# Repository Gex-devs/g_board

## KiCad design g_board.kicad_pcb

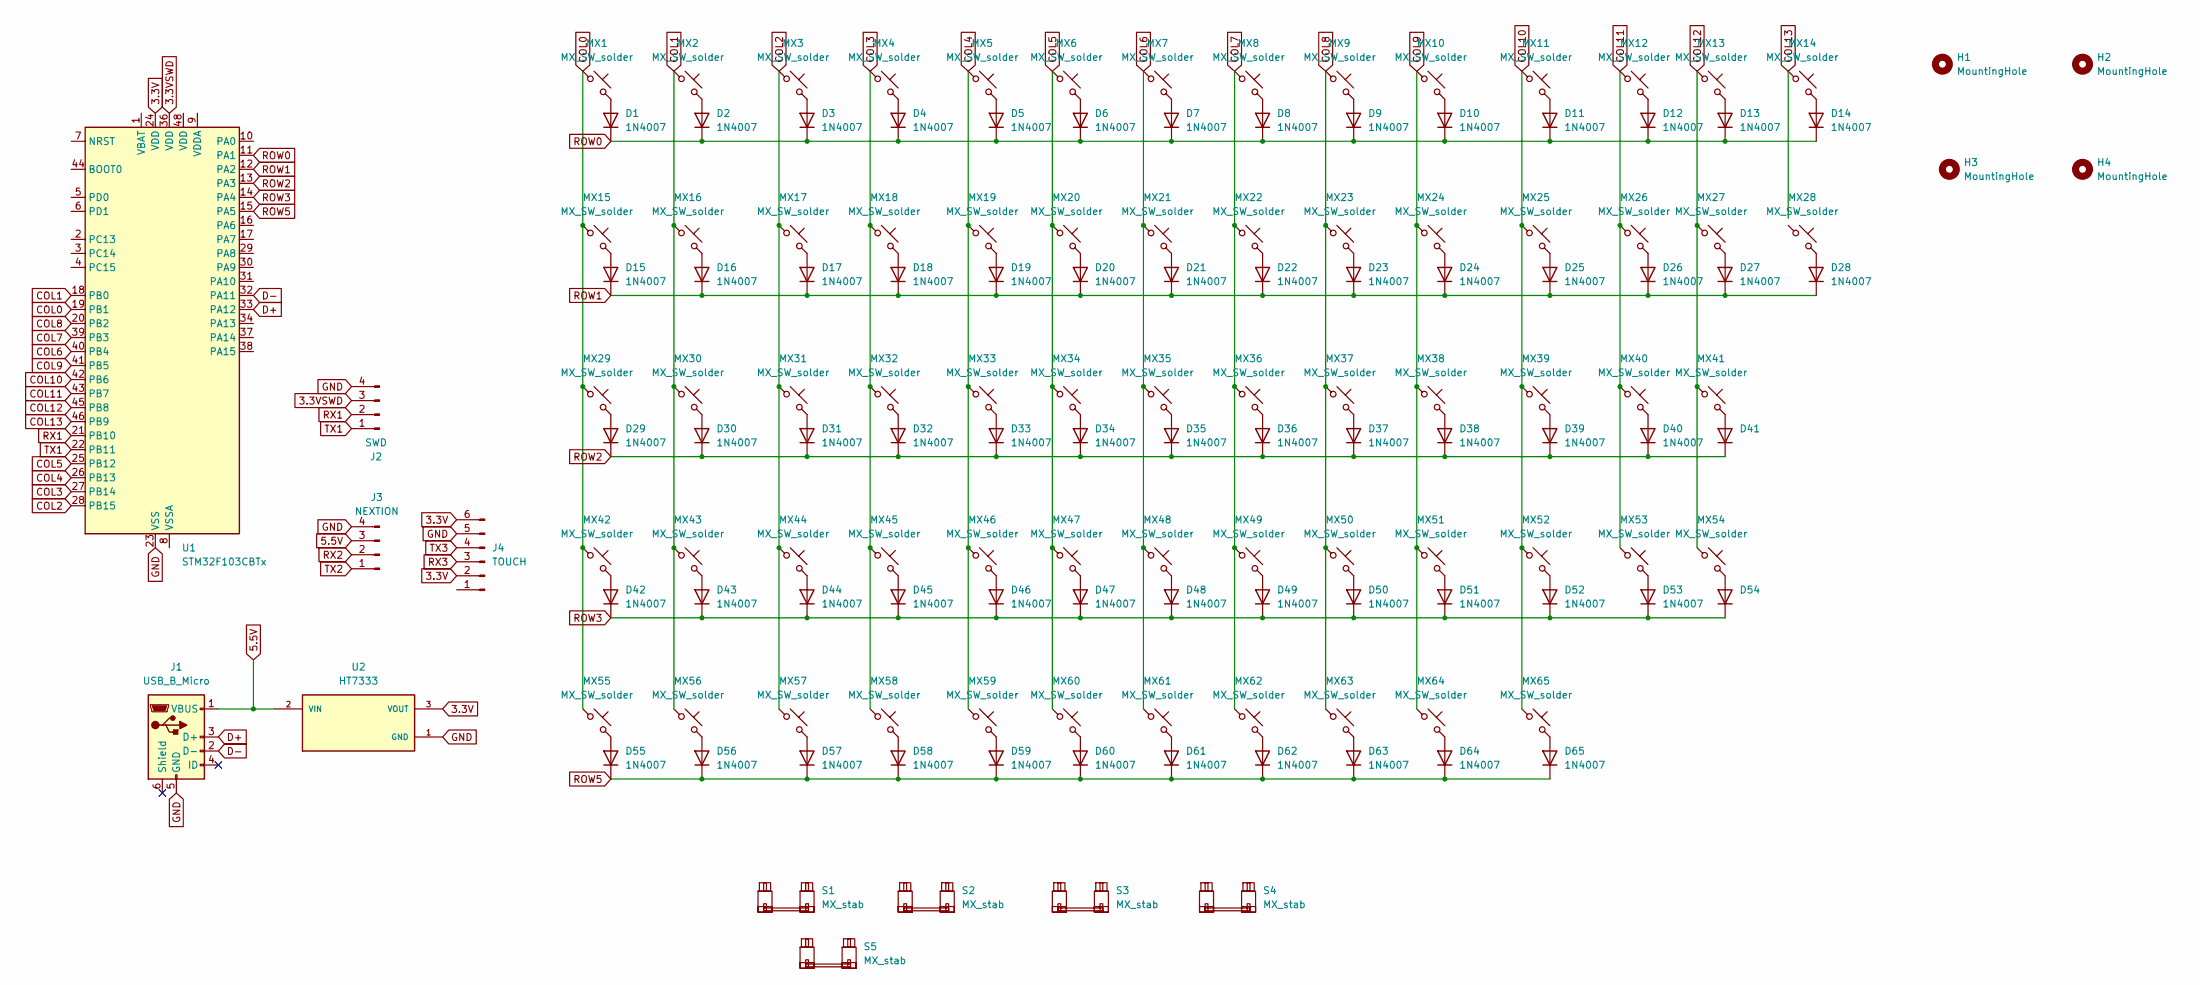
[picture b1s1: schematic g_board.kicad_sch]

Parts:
D1, D2, D3, D4, D5, D6, D7, D8, D9, D10, D11, D12, D13, D14, D15, D16, D17, D18, D19, D20, D21, D22, D23, D24, D25, D26, D27, D28, D29, D30, D31, D32, D33, D34, D35, D36, D37, D38, D39, D40, D41, D42, D43, D44, D45, D46, D47, D48, D49, D50, D51, D52, D53, D54, D55, D56, D57, D58, D59, D60, D61, D62, D63, D64, D65: 1N4007; D_DO-41_SOD81_P10.16mm_Horizontal
H1, H2, H3, H4: MountingHole; MountingHole_3.2mm_M3
J1: USB_B_Micro; USB_Micro-AB_Molex_47590-0001
J2: SWD; PinHeader_1x04_P2.54mm_Vertical
J3: NEXTION; PinHeader_1x04_P2.54mm_Vertical
J4: TOUCH; PinSocket_1x06_P2.54mm_Vertical
MX1, MX2, MX3, MX4, MX5, MX6, MX7, MX8, MX9, MX10, MX11, MX12, MX13, MX14, MX16, MX17, MX18, MX19, MX20, MX21, MX22, MX23, MX24, MX25, MX26, MX27, MX30, MX31, MX32, MX33, MX34, MX35, MX36, MX37, MX38, MX39, MX40, MX41, MX42, MX43, MX44, MX45, MX46, MX47, MX48, MX49, MX50, MX51, MX52, MX53, MX54, MX58, MX63, MX64, MX65: MX_SW_solder; SW_MX_1u
MX15, MX28: MX_SW_solder; SW_MX_1.5u
MX29: MX_SW_solder; SW_MX_1.75u
MX55, MX56, MX57, MX59, MX60, MX61, MX62: MX_SW_solder; SW_MX_1.25u
S1: MX_stab; STAB_MX_P_6.25u
S2: MX_stab; STAB_MX_P_2.75u
S3: MX_stab; STAB_MX_P_2u
S4, S5: MX_stab; STAB_MX_P_2.25u
U1: STM32F103CBTx; LQFP-48_7x7mm_P0.5mm
U2: HT7333; IC_HT7333; PARTREV 1.80

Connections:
3.3V: J4.2, J4.6, U1.24 (VDD), U2.3 (VOUT)
3.3VSWD: J2.3, U1.36 (VDD)
5.5V: J1.1 (VBUS), J3.3, U2.2 (VIN)
COL0: MX1.1, MX15.1, MX29.1, MX42.1, MX55.1, U1.19 (PB1)
COL1: MX2.1, MX16.1, MX30.1, MX43.1, MX56.1, U1.18 (PB0)
COL2: MX3.1, MX17.1, MX31.1, MX44.1, MX57.1, U1.28 (PB15)
COL3: MX4.1, MX18.1, MX32.1, MX45.1, MX58.1, U1.27 (PB14)
COL4: MX5.1, MX19.1, MX33.1, MX46.1, MX59.1, U1.26 (PB13)
COL5: MX6.1, MX20.1, MX34.1, MX47.1, MX60.1, U1.25 (PB12)
COL6: MX7.1, MX21.1, MX35.1, MX48.1, MX61.1, U1.40 (PB4)
COL7: MX8.1, MX22.1, MX36.1, MX49.1, MX62.1, U1.39 (PB3)
COL8: MX9.1, MX23.1, MX37.1, MX50.1, MX63.1, U1.20 (PB2)
COL9: MX10.1, MX24.1, MX38.1, MX51.1, MX64.1, U1.41 (PB5)
COL10: MX11.1, MX25.1, MX39.1, MX52.1, MX65.1, U1.42 (PB6)
COL11: MX12.1, MX26.1, MX40.1, MX53.1, U1.43 (PB7)
COL12: MX13.1, MX27.1, MX41.1, MX54.1, U1.45 (PB8)
COL13: MX14.1, U1.46 (PB9)
D+: J1.3 (D+), U1.33 (PA12)
D-: J1.2 (D-), U1.32 (PA11)
GND: J1.5 (GND), J2.4, J3.4, J4.5, U1.23 (VSS), U1.35 (VSS), U1.47 (VSS), U2.1 (GND)
unnamed: D1.2 (A), MX1.2
unnamed: D2.2 (A), MX2.2
unnamed: D3.2 (A), MX3.2
unnamed: D4.2 (A), MX4.2
unnamed: D5.2 (A), MX5.2
unnamed: D6.2 (A), MX6.2
unnamed: D7.2 (A), MX7.2
unnamed: D8.2 (A), MX8.2
unnamed: D9.2 (A), MX9.2
unnamed: D10.2 (A), MX10.2
unnamed: D11.2 (A), MX11.2
unnamed: D12.2 (A), MX12.2
unnamed: D13.2 (A), MX13.2
unnamed: D14.2 (A), MX14.2
unnamed: D15.2 (A), MX15.2
unnamed: D16.2 (A), MX16.2
unnamed: D17.2 (A), MX17.2
unnamed: D18.2 (A), MX18.2
unnamed: D19.2 (A), MX19.2
unnamed: D20.2 (A), MX20.2
unnamed: D21.2 (A), MX21.2
unnamed: D22.2 (A), MX22.2
unnamed: D23.2 (A), MX23.2
unnamed: D24.2 (A), MX24.2
unnamed: D25.2 (A), MX25.2
unnamed: D26.2 (A), MX26.2
unnamed: D27.2 (A), MX27.2
unnamed: D28.2 (A), MX28.2
unnamed: D29.2 (A), MX29.2
unnamed: D30.2 (A), MX30.2
unnamed: D31.2 (A), MX31.2
unnamed: D32.2 (A), MX32.2
unnamed: D33.2 (A), MX33.2
unnamed: D34.2 (A), MX34.2
unnamed: D35.2 (A), MX35.2
unnamed: D36.2 (A), MX36.2
unnamed: D37.2 (A), MX37.2
unnamed: D38.2 (A), MX38.2
unnamed: D39.2 (A), MX39.2
unnamed: D40.2 (A), MX40.2
unnamed: D41.2 (A), MX41.2
unnamed: D42.2 (A), MX42.2
unnamed: D43.2 (A), MX43.2
unnamed: D44.2 (A), MX44.2
unnamed: D45.2 (A), MX45.2
unnamed: D46.2 (A), MX46.2
unnamed: D47.2 (A), MX47.2
unnamed: D48.2 (A), MX48.2
unnamed: D49.2 (A), MX49.2
unnamed: D50.2 (A), MX50.2
unnamed: D51.2 (A), MX51.2
unnamed: D52.2 (A), MX52.2
unnamed: D53.2 (A), MX53.2
unnamed: D54.2 (A), MX54.2
unnamed: D55.2 (A), MX55.2
unnamed: D56.2 (A), MX56.2
unnamed: D57.2 (A), MX57.2
unnamed: D58.2 (A), MX58.2
unnamed: D59.2 (A), MX59.2
unnamed: D60.2 (A), MX60.2
unnamed: D61.2 (A), MX61.2
unnamed: D62.2 (A), MX62.2
unnamed: D63.2 (A), MX63.2
unnamed: D64.2 (A), MX64.2
unnamed: D65.2 (A), MX65.2
ROW0: D1.1 (K), D2.1 (K), D3.1 (K), D4.1 (K), D5.1 (K), D6.1 (K), D7.1 (K), D8.1 (K), D9.1 (K), D10.1 (K), D11.1 (K), D12.1 (K), D13.1 (K), D14.1 (K), U1.11 (PA1)
ROW1: D15.1 (K), D16.1 (K), D17.1 (K), D18.1 (K), D19.1 (K), D20.1 (K), D21.1 (K), D22.1 (K), D23.1 (K), D24.1 (K), D25.1 (K), D26.1 (K), D27.1 (K), D28.1 (K), U1.12 (PA2)
ROW2: D29.1 (K), D30.1 (K), D31.1 (K), D32.1 (K), D33.1 (K), D34.1 (K), D35.1 (K), D36.1 (K), D37.1 (K), D38.1 (K), D39.1 (K), D40.1 (K), D41.1 (K), U1.13 (PA3)
ROW3: D42.1 (K), D43.1 (K), D44.1 (K), D45.1 (K), D46.1 (K), D47.1 (K), D48.1 (K), D49.1 (K), D50.1 (K), D51.1 (K), D52.1 (K), D53.1 (K), D54.1 (K), U1.14 (PA4)
ROW5: D55.1 (K), D56.1 (K), D57.1 (K), D58.1 (K), D59.1 (K), D60.1 (K), D61.1 (K), D62.1 (K), D63.1 (K), D64.1 (K), D65.1 (K), U1.15 (PA5)
RX1: J2.2, U1.21 (PB10)
RX2: J3.2
RX3: J4.3
TX1: J2.1, U1.22 (PB11)
TX2: J3.1
TX3: J4.4

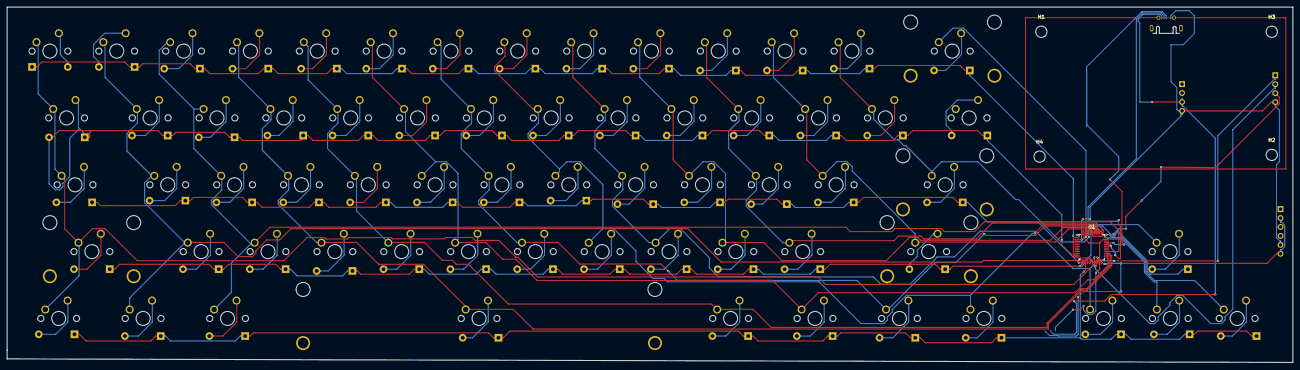
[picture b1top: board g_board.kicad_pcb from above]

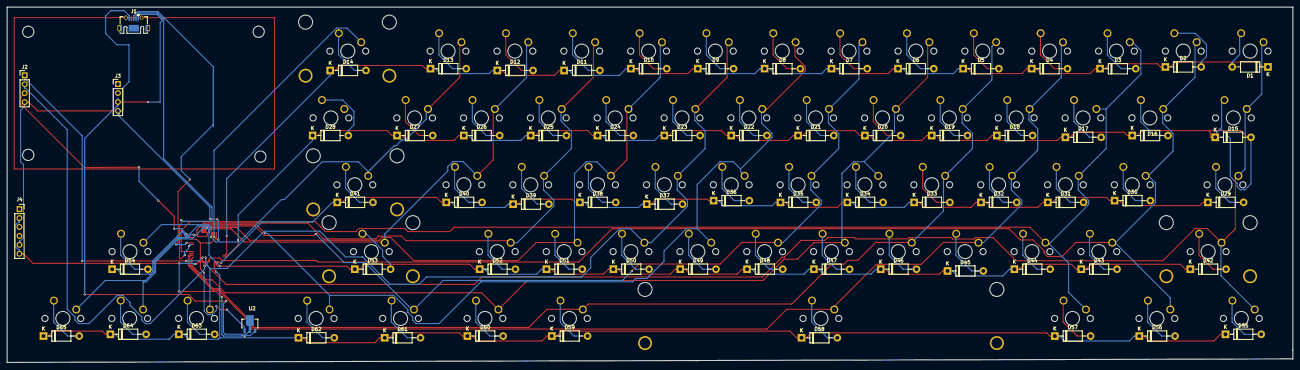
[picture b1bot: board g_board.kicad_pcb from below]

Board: 2 copper layers, 365.4 x 100.9 mm, 145 parts (70 on the bottom side), 92 nets.
